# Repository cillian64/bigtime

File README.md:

# bigtime
A rather large wall clock using big 7-segment displays, powered by 802.3af
power-over-ethernet, and synchronised using NTP over wired ethernet.
Configuration is done using an interactive USB shell and stored in flash.

One of these clocks is deployed in each of Lecture Theatres 1 and 2 at the
[Department of Computer Science and Technology](https://www.cst.cam.ac.uk/)
(formerly known as the [Computer Lab](https://www.cl.cam.ac.uk/)), [University
of Cambridge](https://www.cam.ac.uk/), UK.

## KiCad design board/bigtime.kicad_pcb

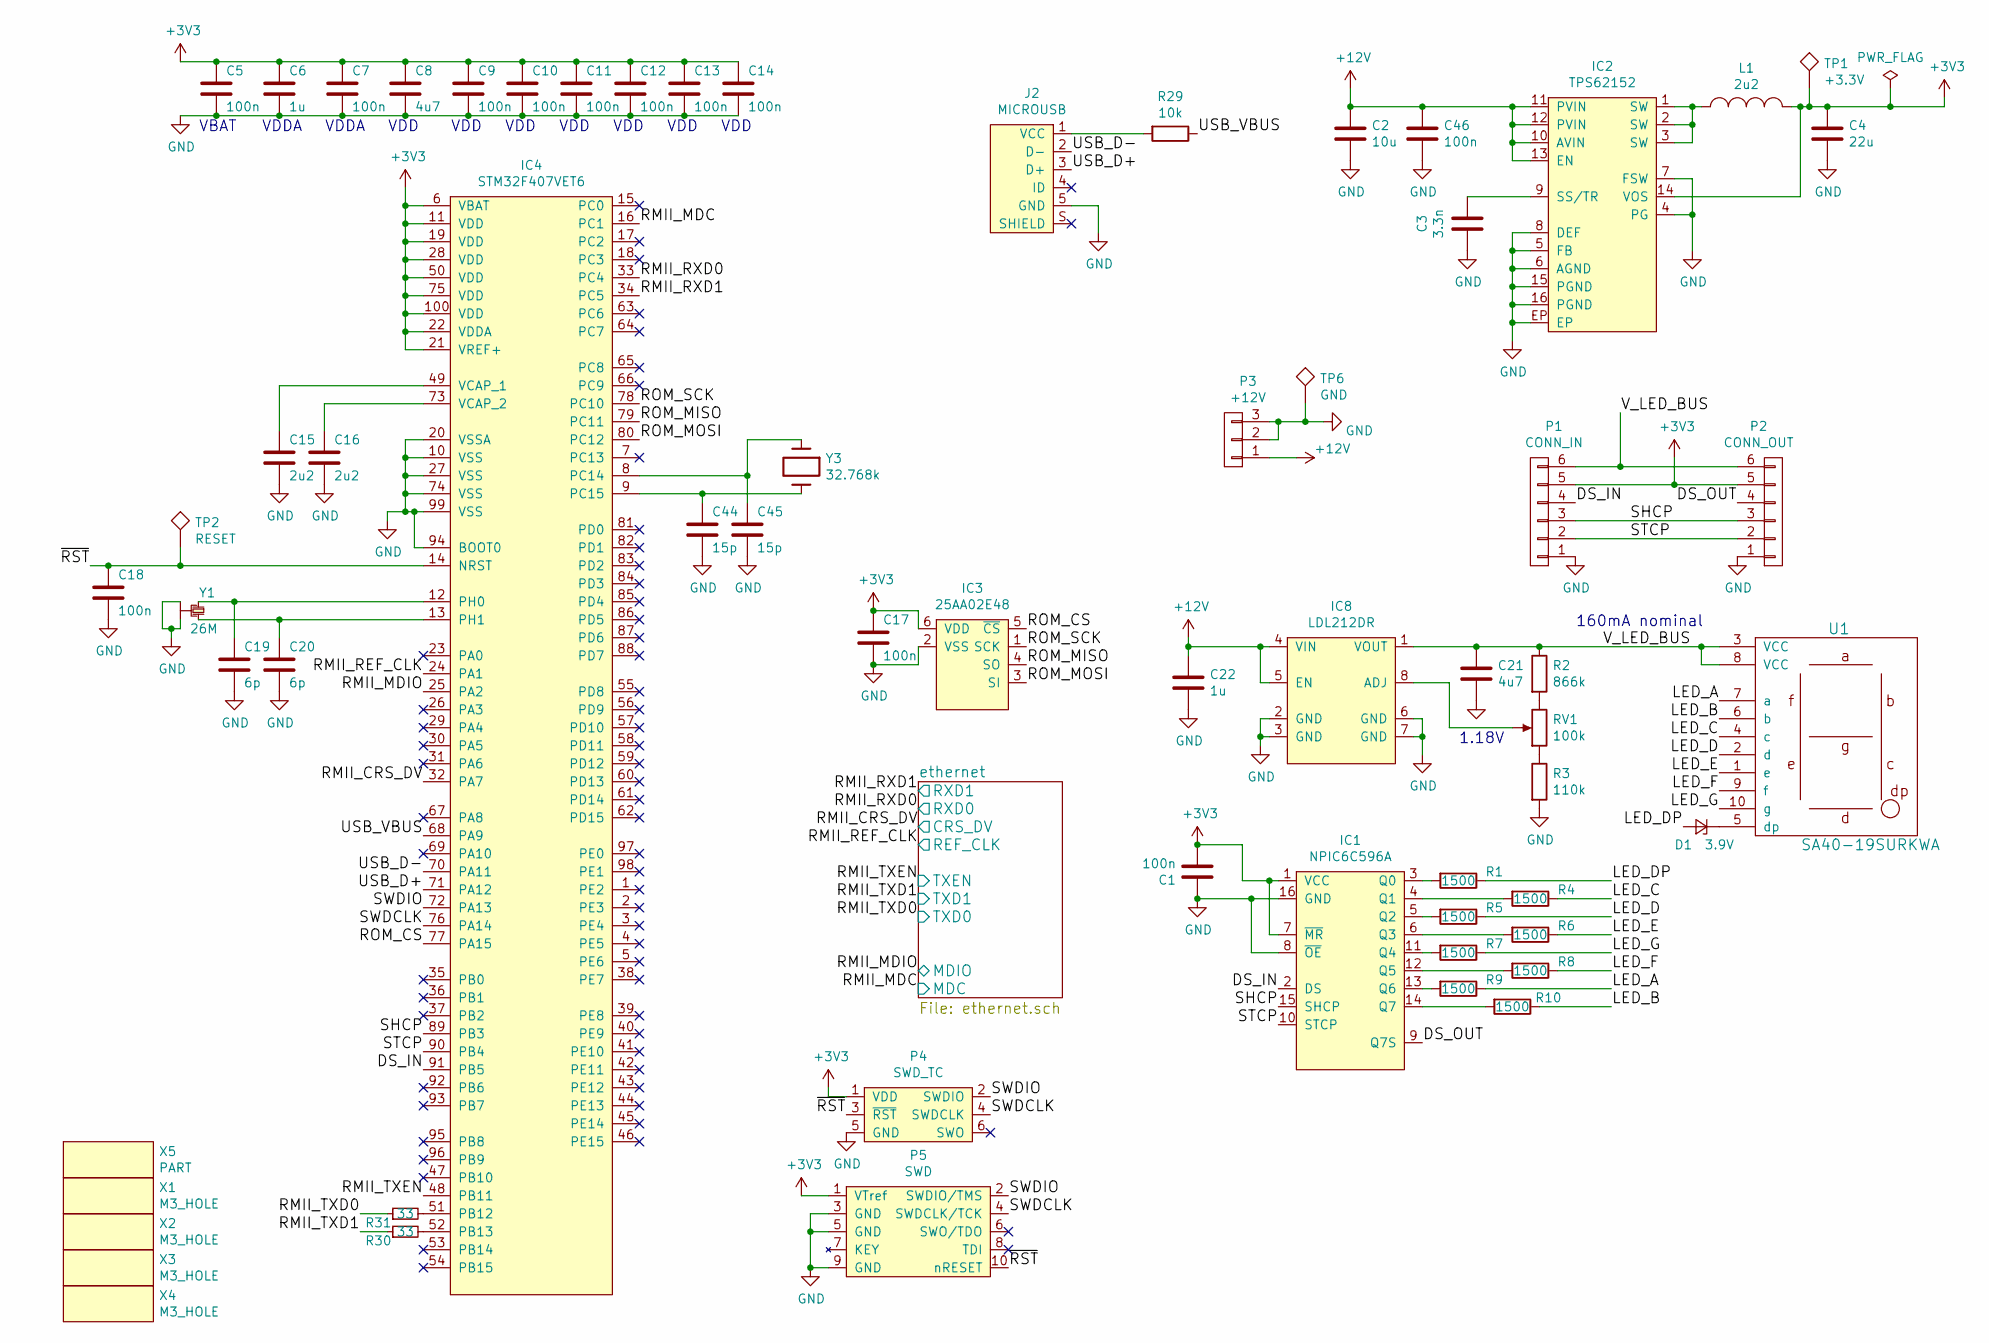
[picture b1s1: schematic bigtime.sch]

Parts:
C1, C5, C7, C9, C10, C11, C12, C13, C14, C17, C18, C46: 100n; 0603
C2: 10u; 0603; Farnell 2494230
C3: 3.3n; 0603; Farnell 2496853
C4: 22u; 0603; Farnell 2494232
C6, C22: 1u; 0603
C8, C21: 4u7; 0603
C15, C16: 2u2; 0603
C19, C20: 6p; 0603
C44, C45: 15p; 0603
D1: 3.9V; SOD-323; Farnell 8735662
IC1: NPIC6C596A; TSSOP-16; Farnell 2445196
IC2: TPS62152; QFN-16-EP-TI; Farnell 2382918
IC3: 25AA02E48; SOT-23-6; Farnell 1700995
IC4: STM32F407VET6; LQFP-100; Farnell 2064367
IC8: LDL212DR; SOIC-8; Farnell 2630956
J2: MICROUSB; MICROUSB_MOLEX_47589-0001; Farnell 1568023
L1: 2u2; L2520; Farnell 2543271
P1: CONN_IN; IDC_Header_Straight_6pins
P2: CONN_OUT; IDC_Header_Straight_6pins
P3: +12V; BARREL_JACK
P4: SWD_TC; TC2030-NL
P5: SWD; FTSH-105-01-F-D-K
R1, R4, R5, R6, R7, R8, R9, R10: 1500; 0603; Farnell 9233407
R2: 866k; 0603; Farnell 2303318
R3: 110k; 0603; Farnell 2502402
R29: 10k; 0603
R30, R31: 33; 0603
RV1: 100k; 3386P; Farnell 9355049
TP1: +3.3V; SIL-254P-01
TP2: RESET; SIL-254P-01
TP6: GND; SIL-254P-01
U1: SA40-19SURKWA; SA40-18; Farnell 2080056
X1, X2, X3, X4: M3_HOLE; M3_MOUNT
X5: PART; Polarity_Center_Positive_6mm_SilkScreen
Y1: 26M; XTAL-20x16; Farnell 2455834
Y3: 32.768k; XTAL_1206; Farnell 2101347

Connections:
+3V3: C1.2, C4.1, C5.1, C6.1, C7.1, C8.1, C9.1, C10.1, C11.1, C12.1, C13.1, C14.1, C17.1, IC1.1 (VCC), IC1.7 (~MR), IC2.14 (VOS), IC3.6 (VDD), IC4.6 (VBAT), IC4.11 (VDD), IC4.19 (VDD), IC4.21 (VREF+), IC4.22 (VDDA), IC4.28 (VDD), IC4.50 (VDD), IC4.75 (VDD), IC4.100 (VDD), L1.2, P1.5, P2.5, P4.1 (VDD), P5.1 (VTref), TP1.1; also elsewhere on the board
+12V: C2.1, C22.2, C46.1, IC2.10 (AVIN), IC2.11 (PVIN), IC2.12 (PVIN), IC2.13 (EN), IC8.4 (VIN), IC8.5 (EN), P3.1; also elsewhere on the board
/DS_IN: IC1.2 (DS), IC4.91 (PB5), P1.4
/DS_OUT: IC1.9 (Q7S), P2.4
/LED_A: R9.1, U1.7 (a)
/LED_B: R10.1, U1.6 (b)
/LED_C: R4.1, U1.4 (c)
/LED_D: R5.1, U1.2 (d)
/LED_DP: D1.2 (A), R1.1
/LED_E: R6.1, U1.1 (e)
/LED_F: R8.1, U1.9 (f)
/LED_G: R7.1, U1.10 (g)
/RMII_CRS_DV: IC4.32 (PA7); also elsewhere on the board
/RMII_MDC: IC4.16 (PC1); also elsewhere on the board
/RMII_MDIO: IC4.25 (PA2); also elsewhere on the board
/RMII_REF_CLK: IC4.24 (PA1); also elsewhere on the board
/RMII_RXD0: IC4.33 (PC4); also elsewhere on the board
/RMII_RXD1: IC4.34 (PC5); also elsewhere on the board
/RMII_TXD0: R31.1; also elsewhere on the board
/RMII_TXD1: R30.1; also elsewhere on the board
/RMII_TXEN: IC4.48 (PB11); also elsewhere on the board
/ROM_CS: IC3.5 (~CS), IC4.77 (PA15)
/ROM_MISO: IC3.4 (SO), IC4.79 (PC11)
/ROM_MOSI: IC3.3 (SI), IC4.80 (PC12)
/ROM_SCK: IC3.1 (SCK), IC4.78 (PC10)
/SHCP: IC1.15 (SHCP), IC4.89 (PB3), P1.3, P2.3
/STCP: IC1.10 (STCP), IC4.90 (PB4), P1.2, P2.2
/SWDCLK: IC4.76 (PA14), P4.4 (SWDCLK), P5.4 (SWDCLK/TCK)
/SWDIO: IC4.72 (PA13), P4.2 (SWDIO), P5.2 (SWDIO/TMS)
/USB_D+: IC4.71 (PA12), J2.3 (D+)
/USB_D-: IC4.70 (PA11), J2.2 (D-)
/USB_VBUS: IC4.68 (PA9), R29.1
/V_LED_BUS: C21.1, IC8.1 (VOUT), P1.6, P2.6, R2.1, U1.3 (VCC), U1.8 (VCC)
/~RST: C18.1, IC4.14 (NRST), P4.3 (~RST), P5.10 (nRESET), TP2.1
GND: C1.1, C2.2, C3.2, C4.2, C5.2, C6.2, C7.2, C8.2, C9.2, C10.2, C11.2, C12.2, C13.2, C14.2, C15.2, C16.2, C17.2, C18.2, C19.2, C20.2, C21.2, C22.1, C44.2, C45.2, C46.2, IC1.8 (~OE), IC1.16 (GND), IC2.4 (PG), IC2.5 (FB), IC2.6 (AGND), IC2.7 (FSW), IC2.8 (DEF), IC2.15 (PGND), IC2.16 (PGND), IC2.EP, IC3.2 (VSS), IC4.10 (VSS), IC4.20 (VSSA), IC4.27 (VSS), IC4.74 (VSS), IC4.94 (BOOT0), IC4.99 (VSS), IC8.2 (GND), IC8.3 (GND), IC8.6 (GND), IC8.7 (GND), J2.5 (GND), P1.1, P2.1, P3.2, P3.3, P4.5 (GND), P5.3 (GND), P5.5 (GND), P5.9 (GND), R3.2, TP6.1, Y1.2, Y1.4; also elsewhere on the board
unnamed: C3.1, IC2.9 (SS/TR)
unnamed: C15.1, IC4.49 (VCAP_1)
unnamed: C16.1, IC4.73 (VCAP_2)
unnamed: C19.1, IC4.12 (PH0), Y1.1
unnamed: C20.1, IC4.13 (PH1), Y1.3
unnamed: C44.1, IC4.9 (PC15), Y3.2
unnamed: C45.1, IC4.8 (PC14), Y3.1
unnamed: D1.1 (K), U1.5 (dp)
unnamed: IC1.3 (Q0), R1.2
unnamed: IC1.4 (Q1), R4.2
unnamed: IC1.5 (Q2), R5.2
unnamed: IC1.6 (Q3), R6.2
unnamed: IC1.11 (Q4), R7.2
unnamed: IC1.12 (Q5), R8.2
unnamed: IC1.13 (Q6), R9.2
unnamed: IC1.14 (Q7), R10.2
unnamed: IC2.1 (SW), IC2.2 (SW), IC2.3 (SW), L1.1
unnamed: IC4.51 (PB12), R31.2
unnamed: IC4.52 (PB13), R30.2
unnamed: IC8.8 (ADJ), RV1.2
unnamed: J2.1 (VCC), R29.2
unnamed: R2.2, RV1.3
unnamed: R3.1, RV1.1

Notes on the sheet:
160mA nominal
VBAT
VDDA
VDD
1.18V

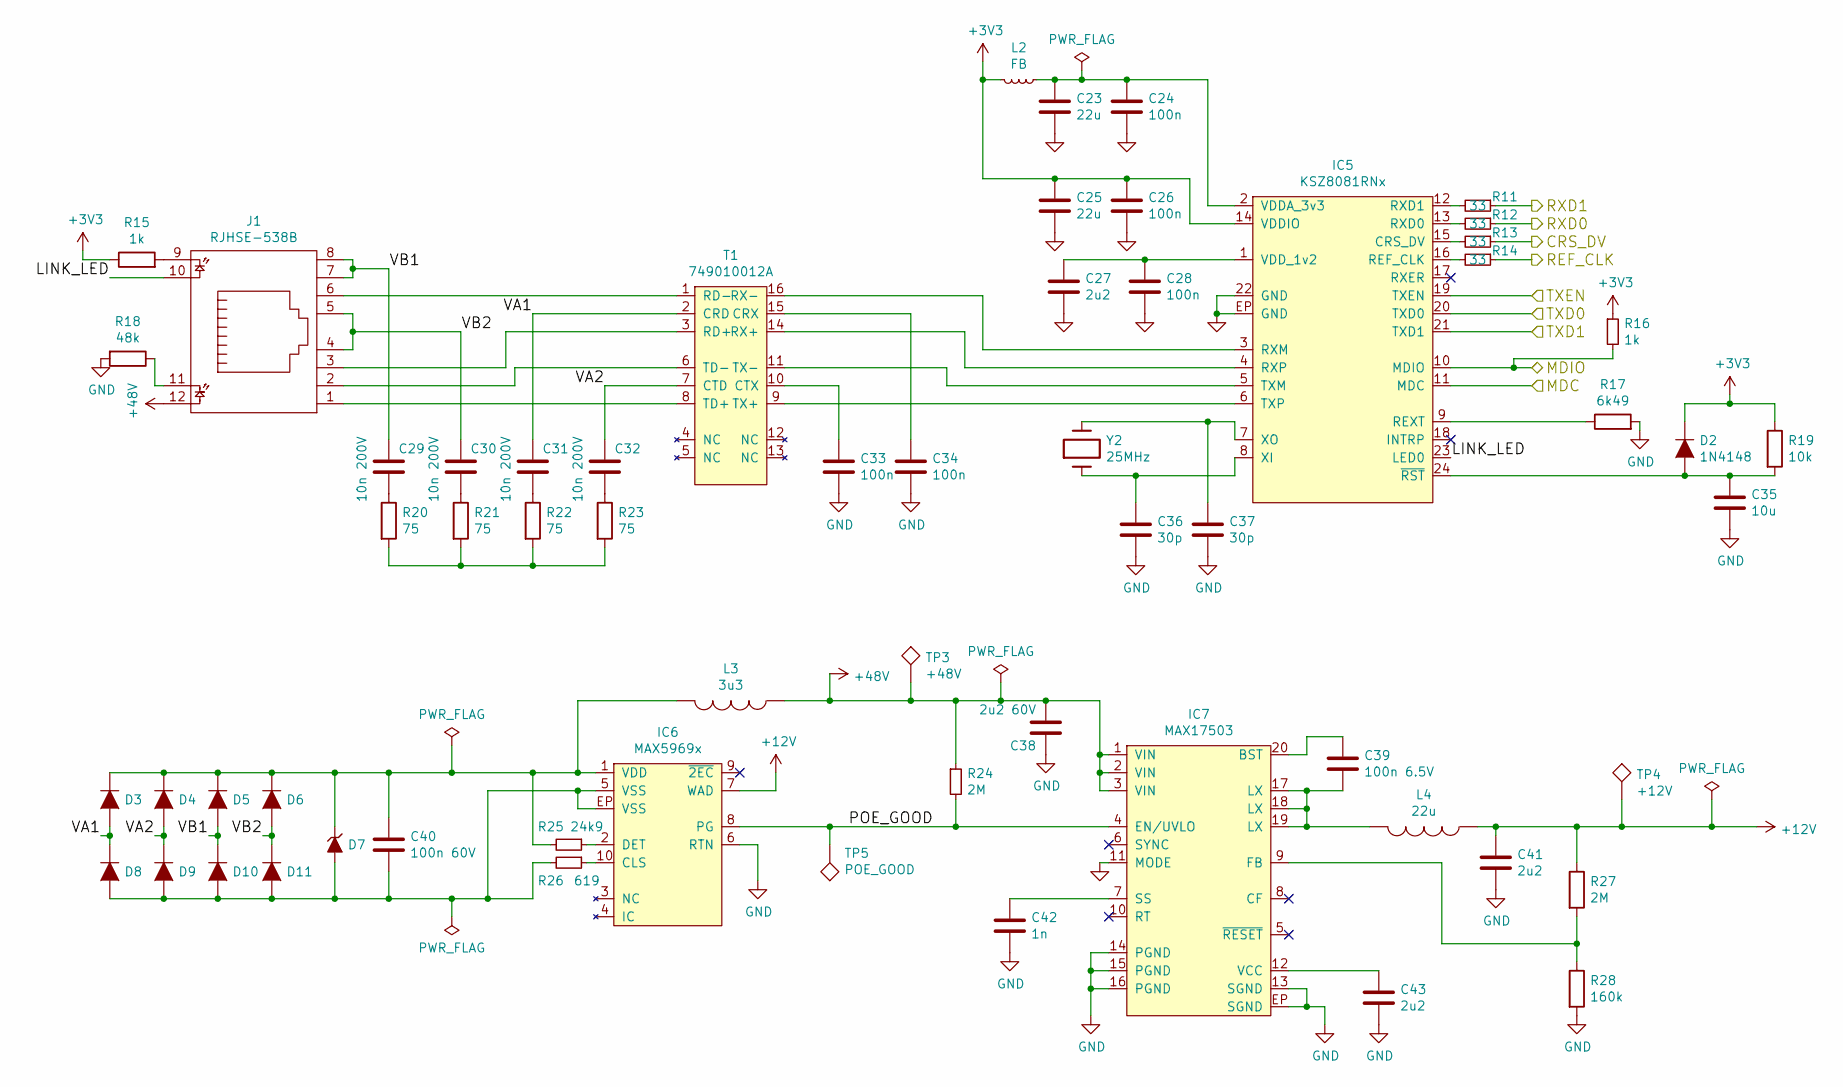
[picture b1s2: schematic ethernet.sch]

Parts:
C23, C25: 22u; 0603; Farnell 2494232
C24, C26, C28, C33, C34: 100n; 0603
C27: 2u2; 0603
C29, C30, C31, C32: 10n 200V; 0805; Farnell 1828955
C35: 10u; 0603
C36, C37: 30p; 0603
C38: 2u2 60V; 1210; Farnell 2579024
C39: 100n 6.5V; 0603
C40: 100n 60V; 0805; Farnell 2496941
C41, C43: 2u2; 0603; Farnell 1735526
C42: 1n; 0603
D2: 1N4148; SOD-323
D3, D4, D5, D6, D8, D9, D10, D11: SS110B; DO-214AA-SMB
D7: SMAJ58A; DO-214AC-SMA
IC5: KSZ8081RNx; QFN-24-EP-MICREL; Farnell 2509802
IC6: MAX5969x; DFN-10-EP-MAX; Farnell 2514586
IC7: MAX17503; QFN-20-EP-MAX; Farnell 2514229
J1: RJHSE-538B; RJHSE538X; Farnell 1860592
L2: FB; 0603
L3: 3u3; ELLATP3R3NB; Farnell 1865686
L4: 22u; SRR1260A; Farnell 1929699
R11, R12, R13, R14: 33; 0603
R15, R16: 1k; 0603
R17: 6k49; 0603
R18: 48k; 0603
R19: 10k; 0603
R20, R21, R22, R23: 75; 0603
R24, R27: 2M; 0603; Farnell 2502428
R25: 24k9; 0603
R26: 619; 0603
R28: 160k; 0603; Farnell 2670652
T1: 749010012A; Farnell 2422552
TP3: +48V; SIL-254P-01
TP4: +12V; SIL-254P-01
TP5: POE_GOOD; SIL-254P-01
Y2: 25MHz; XTAL-50x32

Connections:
+3V3: C25.1, C26.1, D2.1 (K), IC5.14 (VDDIO), L2.2, R15.1, R16.1, R19.1; also elsewhere on the board
+12V: C41.1, IC6.7 (WAD), L4.1, R27.1, TP4.1; also elsewhere on the board
+48V: C38.2, IC7.1 (VIN), IC7.2 (VIN), IC7.3 (VIN), J1.12, L3.1, R24.1, TP3.1
/RMII_CRS_DV: R13.1; also elsewhere on the board
/RMII_MDC: IC5.11 (MDC); also elsewhere on the board
/RMII_MDIO: IC5.10 (MDIO), R16.2; also elsewhere on the board
/RMII_REF_CLK: R14.1; also elsewhere on the board
/RMII_RXD0: R12.1; also elsewhere on the board
/RMII_RXD1: R11.1; also elsewhere on the board
/RMII_TXD0: IC5.20 (TXD0); also elsewhere on the board
/RMII_TXD1: IC5.21 (TXD1); also elsewhere on the board
/RMII_TXEN: IC5.19 (TXEN); also elsewhere on the board
/ethernet/LINK_LED: IC5.23 (LED0), J1.10
/ethernet/POE_GOOD: IC6.8 (PG), IC7.4 (EN/UVLO), R24.2, TP5.1
/ethernet/VA1: C31.1, D3.2 (A), D8.1 (K), T1.2 (CRD)
/ethernet/VA2: C32.1, D4.2 (A), D9.1 (K), T1.7 (CTD)
/ethernet/VB1: C29.1, D5.2 (A), D10.1 (K), J1.7, J1.8
/ethernet/VB2: C30.1, D6.2 (A), D11.1 (K), J1.4, J1.5
GND: C23.2, C24.2, C25.2, C26.2, C27.2, C28.2, C33.2, C34.2, C35.2, C36.2, C37.2, C38.1, C41.2, C42.2, C43.2, IC5.22 (GND), IC5.EP (GND), IC6.6 (RTN), IC7.11 (MODE), IC7.13 (SGND), IC7.14 (PGND), IC7.15 (PGND), IC7.16 (PGND), IC7.EP (SGND), R17.2, R18.2, R28.2; also elsewhere on the board
unnamed: C23.1, C24.1, IC5.2 (VDDA_3v3), L2.1
unnamed: C27.1, C28.1, IC5.1 (VDD_1v2)
unnamed: C29.2, R20.1
unnamed: C30.2, R21.1
unnamed: C31.2, R22.1
unnamed: C32.2, R23.1
unnamed: C33.1, T1.10 (CTX)
unnamed: C34.1, T1.15 (CRX)
unnamed: C35.1, D2.2 (A), IC5.24 (~RST), R19.2
unnamed: C36.1, IC5.8 (XI), Y2.1
unnamed: C37.1, IC5.7 (XO), Y2.2
unnamed: C39.1, IC7.20 (BST)
unnamed: C39.2, IC7.17 (LX), IC7.18 (LX), IC7.19 (LX), L4.2
unnamed: C40.1, D3.1 (K), D4.1 (K), D5.1 (K), D6.1 (K), D7.1 (K), IC6.1 (VDD), L3.2, R25.2
unnamed: C40.2, D7.2 (A), D8.2 (A), D9.2 (A), D10.2 (A), D11.2 (A), IC6.5 (VSS), IC6.EP (VSS), R26.2
unnamed: C42.1, IC7.7 (SS)
unnamed: C43.1, IC7.12 (VCC)
unnamed: IC5.3 (RXM), T1.16 (RX-)
unnamed: IC5.4 (RXP), T1.14 (RX+)
unnamed: IC5.5 (TXM), T1.11 (TX-)
unnamed: IC5.6 (TXP), T1.9 (TX+)
unnamed: IC5.9 (REXT), R17.1
unnamed: IC5.12 (RXD1), R11.2
unnamed: IC5.13 (RXD0), R12.2
unnamed: IC5.15 (CRS_DV), R13.2
unnamed: IC5.16 (REF_CLK), R14.2
unnamed: IC6.2 (DET), R25.1
unnamed: IC6.10 (CLS), R26.1
unnamed: IC7.9 (FB), R27.2, R28.1
unnamed: J1.1, T1.8 (TD+)
unnamed: J1.2, T1.6 (TD-)
unnamed: J1.3, T1.3 (RD+)
unnamed: J1.6, T1.1 (RD-)
unnamed: J1.9, R15.2
unnamed: J1.11, R18.1
unnamed: R20.2, R21.2, R22.2, R23.2

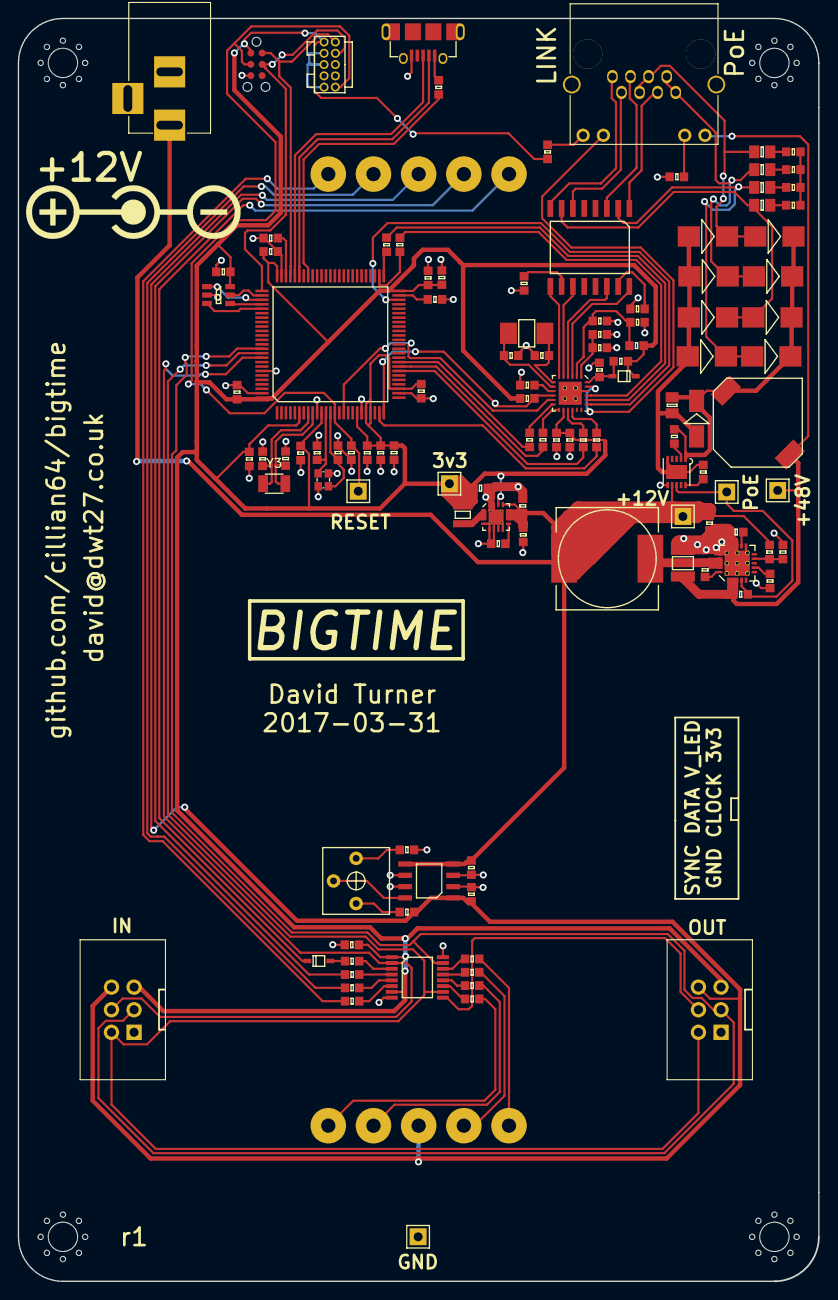
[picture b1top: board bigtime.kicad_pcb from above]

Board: 2 copper layers, 90.0 x 142.0 mm, 124 parts (1 on the bottom side), 101 nets.

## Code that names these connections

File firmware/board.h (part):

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 *  GPIOA setup:
 *
 * PA0  - PIN0                         (unused).
 * PA1  - RMII_REF_CLK                 (af11).
 * PA2  - RMII_MDIO                    (af11).
 * PA3  - PIN3                         (unused).
 * PA4  - PIN4                         (unused).
 * PA5  - PIN5                         (unused).
 * PA6  - PIN6                         (unused).
 * PA7  - RMII_CRS_DV                  (af11).
 * PA8  - PIN8                         (unused).
 * PA9  - USB_VBUS                     (input, pulldown).
 * PA10 - PIN10                        (unused).
 * PA11 - USB_DM                       (af10).
 * PA12 - USB_DP                       (af10).
 * PA13 - SWDIO                        (af0, pulldown).
 * PA14 - SWCLK                        (af0, pulldown).
 * PA15 - ROM_CS                       (output, starthigh).
*/
#define VAL_GPIOA_MODER                (PIN_MODE_INPUT(GPIOA_PIN0) | \
                                        PIN_MODE_ALTERNATE(GPIOA_RMII_REF_CLK) | \
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 * PB0  - PIN0                         (unused).
 * PB1  - PIN1                         (unused).
 * PB2  - PIN2                         (unused).
 * PB3  - SHCP                         (af5).
 * PB4  - STCP                         (startlow, output).
 * PB5  - DS                           (af5).
 * PB6  - PIN6                         (unused).
 * PB7  - PIN7                         (unused).
 * PB8  - PIN8                         (unused).
 * PB9  - PIN9                         (unused).
 * PB10 - PIN10                        (unused).
 * PB11 - RMII_TX_EN                   (af11).
 * PB12 - RMII_TXD0                    (af11).
 * PB13 - RMII_TXD1                    (af11).
 * PB14 - PIN14                        (unused).
 * PB15 - PIN15                        (unused).
*/
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 *  GPIOC setup:
 *
 * PC0  - PIN0                         (unused).
 * PC1  - RMII_MDC                     (af11).
 * PC2  - PIN2                         (unused).
 * PC3  - PIN3                         (unused).
 * PC4  - RMII_RXD0                    (af11).
 * PC5  - RMII_RXD1                    (af11).
 * PC6  - PIN6                         (unused).
 * PC7  - PIN7                         (unused).
 * PC8  - PIN8                         (unused).
 * PC9  - PIN9                         (unused).
 * PC10 - ROM_SCK                      (af6).
 * PC11 - ROM_MISO                     (af6).
 * PC12 - ROM_MOSI                     (af6).
 * PC13 - PIN13                        (unused).
 * PC14 - PIN14                        (unused).
 * PC15 - PIN15                        (unused).
*/
#define VAL_GPIOC_MODER                (PIN_MODE_INPUT(GPIOC_PIN0) | \
                                        PIN_MODE_ALTERNATE(GPIOC_RMII_MDC) | \
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/*
 *  GPIOH setup:
 *
 * PH0  - PIN0                         (unused).
 * PH1  - PIN1                         (unused).
 * PH2  - PIN2                         (unused).
 * PH3  - PIN3                         (unused).
 * PH4  - PIN4                         (unused).
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
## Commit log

2017-02-21 Did schematic, sketched board
2017-02-21 bump agg-kicad for npic6c596a
2017-02-21 Added limit resistors
2017-02-21 Rectangular board because life's too short
2017-02-21 Don't forget the mounting holes!
2017-03-01 added some ethernet bits
2017-03-01 bump agg-kicad for kicad nightly fix
2017-03-01 Rescued and fixed library paths
2017-03-01 separate sheet for ethernet
2017-03-03 Roughed out ethernet sheet
2017-03-05 Values for ethernet and max17503
2017-03-06 STM32 support and 25EE MAC chip
2017-03-24 test points, footprints, usb
2017-03-27 Specced part for brightness trimpot
2017-03-28 New LDO, new dimmer network, zener
2017-03-28 bump agg-kicad, position mechanical connectors
2017-03-28 Rough first go at placement minus some shrapnel
2017-03-29 nearly done first route
2017-03-29 Finished first (pretty awful) route
2017-03-30 Tidied SMPS layouts
2017-03-30 Made capacitors more consistent in vals+fps
2017-03-30 Fixed ERC with liberal application of pwr_flag
2017-03-30 Tidied top half of board
2017-03-30 Beefed 12V and V_LED_BUS
2017-03-31 Finished cleaning routing, rounded corners
2017-03-31 Final finishing touches and gerbers
2017-03-31 more silk fiddling
2017-03-31 Reduce mask clearance, budge connectors up
2017-03-31 Removed MAC from silk
2017-03-31 rename edge cuts for dirtypcbs
2017-03-31 Order codes for capacitor shrapnel
2017-03-31 specced remaining parts
2017-04-02 Firmware initial commit: it builds!
2017-04-03 firmware logic thoughts
2017-04-03 More KoD details
2017-04-03 Automatic adjustment will be for BST specifically
2017-04-03 Add seconds+milliseconds display options
2017-04-06 Add SNTP demo software (broke though)
2017-04-06 Fix build error on linux
    Turns out `unix' isa numerical constant on linux but not osx
2017-04-06 Made it actually work (flags and endianness)
2017-04-06 Define src and dst ports
2017-04-07 Various BOMs
2017-04-07 Display driver in progress
2017-04-07 More portable 64-bit endian flip
2017-04-07 Separated test_sntp from sntp.c
2017-04-08 Integrated skeleton RTC and LWIP SNTP client
2017-04-08 Add timeout to SNTP demo software
2017-04-08 In theory, finished RTC handling code
2017-04-09 Basic USB shell (thanks jonsowman & adamgreig)
2017-04-09 Added flash config struct load/save (thadamgreig)
2017-04-09 show and set commands for configuring.
2017-04-09 Add stubs for netinfo+status cmds
2017-04-10 began is_bst
2017-04-10 finished is_bst. I think
2017-04-10 DHCP, DNS configuration
2017-04-10 netinfo command, and DHCP INFORM
2017-04-12 Add epoch and datetime shell commands
2017-04-12 Added state struct & status command
2017-04-20 Added skeleton of tester script
2017-04-22 Simple threade ntpserv for tester
2017-04-22 thread attribute instead of subclassing
2017-04-22 Add locking, declare vars in init, private members
2017-04-22 minor polish
2017-04-22 daemonise ntp thread
2017-04-22 context manager for time_lock
2017-04-25 prototyped tester usb-ser interface
2017-05-05 Remove tests from f/w so it fits in 128k
    Some sort of bug means I can only program the first 128k sector of flash using
    the BMP programmer. As a workaround removing various bits makes the firmware
    small enough to fit. Thanks Adam for this.
2017-05-05 Make DHCP client work
2017-05-05 stickerbom
2017-05-22 Add make power/unpower
2017-05-22 Limit flash section to 128k
    The BMP has issues if we try and program past the first 128k sector on this
    chip. So set the linker script to limit the flash space to 128k so we get a
    linker error if our code gets too big.
2017-05-22 Display now works, counting demo
2017-05-22 Removed seconds & DP sep, display test
    Display test code all works now. Also fixed digit ordering issues. Removed
    seconds because it was complicating things and I'm never going to make a 6
    digit version. Removed DP separator because I now have the separate colon board
2017-05-22 Disable sub-second sync in set_rtc
2017-05-22 New NTP test firmware
2017-05-22 Fix buffering issue with usb shell
    Responses from USB Shell were being buffered and not sent until a few hundred
    characters were received. Replacing jon's dongle usb configuration with the
    stock ChibiOS configuration from
    ChibiOS/demos/STM32/RT-STM32F407-OLIMEX_E407-LWIP-FATFS-USB/usbcfg.? fixed the
    problem.
2017-05-22 Fixed off-by-one with day-of-month?
2017-05-23 Bug: config_save swapped flash src/dst addr
2017-05-23 Use lwip_select for timeout, close(sockfd)
2017-05-23 Handle unknown setting, fix epoch formatting
2017-05-23 Load config on boot, no longer force DHCP enable
2017-05-23 Various RTC fixes
    Now handles century leap years properly. Fixed various fencepost errors in
    rtc_from_ntp and ntp_from_rtc. And a few other bugsplats.
2017-05-23 Splatted final RTC bug, incorrect y2k leap year
2017-05-23 Add dow (day of week) command
2017-05-24 New display thread with sync indicator
2017-05-24 Do BST conversion in display, not store
    Previously we applied DST/BST when saving the time to the RTC. Now we apply
    the conversion in the display routine, meaning the RTC clock is always in UTC.
2017-05-24 New business logic - in theory finished
2017-05-24 Build usbcfg.c, bump main() stack size
2017-05-24 Hide time on force_sync, i.e. on cold boot
2017-05-24 Add adam's hard-fault stack trace magic thing
2017-05-25 Fixed config memory splatting problem.
    This took most of a day to debug and now I have a headache.
2017-05-26 Send hostname for dhcp bind/inform
2017-05-26 Use timezones for usbshell configuration
2017-05-26 Configurable hostname
2017-05-26 Added sensible defaults if unconfigured
2017-10-09 Add network config
2017-11-23 Updated network config
2017-11-23 Change BMP to /dev/ACM0
2017-11-24 Update description, add photo
2021-10-30 Add built firmware .elf file
2021-10-30 Fix DST bug: actually populate day-of-week field
    Turns out the clocks were doing daylight savings changes on slightly the
    wrong day because they got confused about what day of the week it was.
    This is because I'd not been populating the day-of-week field when
    setting the RTC. I'm not sure if I just forgot or were hoping the RTC
    peripheral would calculate this for me.
    Add a simple function to work out what day of the week it is using

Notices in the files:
firmware/board.h:
ChibiOS - Copyright (C) 2006..2016 Giovanni Di Sirio
Licensed under the Apache License, Version 2.0 (the "License");
